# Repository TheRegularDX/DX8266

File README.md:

# DX8266

The DX8266 is a small, low power WiFi development board based around the ESP-12 module that i designed in my free time. Whith the goal being to test my own abilities at electronics and hardware design, and to make a simple board that is more complex and has more pins than the ESP-01, but simpler and more compact than the NodeMCU.

# Revision 2.0 branch
the original version of the board had many issues, this revision aims to improve on the previous version and adds one extra feature, that being a small 4x4  WS2812b (neopixel) matrix for simple display purposes

## Getting started
plug it in with an usb to serial adapter lol 

## to-do

- [x] improve repo layout or something idk
- [ ] add diagrams and graphical schematics
- [x] add a board usage tutorial
- [ ] improve the readme and make it prettier
- [ ] add badges to the readme to make it look proffesional
      
## to-do for rev 2 board

- [ ] add pinout to the board so its usable without staring at the schematic
- [ ] make it breadboard compatible (how did i mess this up...)
- [ ] improve layout
- [ ] improve silkscreen logo

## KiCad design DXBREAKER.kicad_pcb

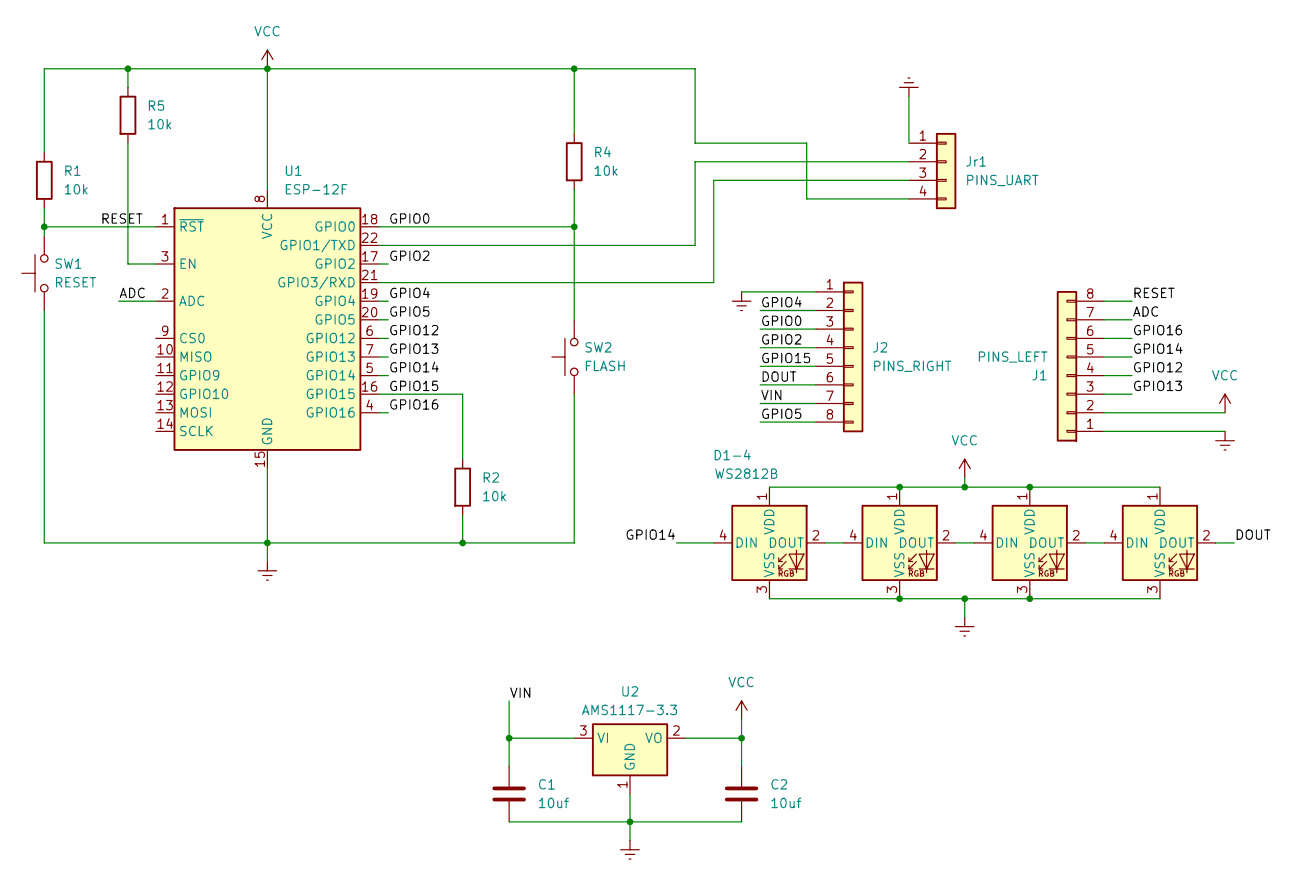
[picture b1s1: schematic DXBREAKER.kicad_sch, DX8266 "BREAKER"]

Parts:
C1, C2: 10uf; C_0805_2012Metric_Pad1.18x1.45mm_HandSolder
D1-4, D2, D3, D4: WS2812B; LED_WS2812B_PLCC4_5.0x5.0mm_P3.2mm
J1: PINS_LEFT; PinSocket_1x08_P2.54mm_Vertical
J2: PINS_RIGHT; PinSocket_1x08_P2.54mm_Vertical
Jr1: PINS_UART; PinSocket_1x04_P2.54mm_Vertical
R1, R2, R4, R5: 10k; R_0805_2012Metric_Pad1.20x1.40mm_HandSolder
SW1: RESET; SW_Push_SPST_NO_Alps_SKRK
SW2: FLASH; SW_Push_SPST_NO_Alps_SKRK
U1: ESP-12F; ESP-12E
U2: AMS1117-3.3; SOT-223-3_TabPin2

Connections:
/ADC: J1.7, U1.2 (ADC)
/DOUT: D4.2 (DOUT), J2.6
/GPIO0: J2.3, R4.2, SW2.2, U1.18 (GPIO0)
/GPIO2: J2.4, U1.17 (GPIO2)
/GPIO4: J2.2, U1.19 (GPIO4)
/GPIO5: J2.8, U1.20 (GPIO5)
/GPIO12: J1.4, U1.6 (GPIO12)
/GPIO13: J1.3, U1.7 (GPIO13)
/GPIO14: D1-4.4 (DIN), J1.5, U1.5 (GPIO14)
/GPIO15: J2.5, R2.1, U1.16 (GPIO15)
/GPIO16: J1.6, U1.4 (GPIO16)
/RESET: J1.8, R1.2, SW1.2, U1.1 (~RST)
/VIN: C1.1, J2.7, U2.3 (VI)
Earth: C1.2, C2.2, D1-4.3 (VSS), D2.3 (VSS), D3.3 (VSS), D4.3 (VSS), J1.1, J2.1, Jr1.1, R2.2, SW1.1, SW2.1, U1.15 (GND), U2.1 (GND); also elsewhere on the board
unnamed: D1-4.2 (DOUT), D2.4 (DIN)
unnamed: D2.2 (DOUT), D3.4 (DIN)
unnamed: D3.2 (DOUT), D4.4 (DIN)
unnamed: Jr1.2, U1.22 (GPIO1/TXD)
unnamed: Jr1.3, U1.21 (GPIO3/RXD)
unnamed: R5.2, U1.3 (EN)
VCC: C2.1, D1-4.1 (VDD), D2.1 (VDD), D3.1 (VDD), D4.1 (VDD), J1.2, Jr1.4, R1.1, R4.1, R5.1, U1.8 (VCC), U2.2 (VO)

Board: 2 copper layers, 18 parts (0 on the bottom side), 21 nets, no tracks yet.

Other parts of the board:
DX: MountingHole_2.2mm_M2_ISO7380_Pad

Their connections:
Earth: DX.1; also elsewhere on the board

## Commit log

2023-09-02 Initial revision of the DX8266 development board
2023-09-02 brrr skibidi dob dob dob yes yes
2023-09-02 Typo
2023-09-03 Update README.md
    more text
2023-09-03 Update README.md
    typo
2023-09-03 i think i updated something
2023-09-03 something idk
2023-09-03 added gitignore
2023-09-03 balls
2023-09-03 updated REEEEEADME
2023-10-24 oopsie
2023-10-25 this fp-info-cache file keeps popping up
2023-10-25 new board layout, added neopixel matrix
